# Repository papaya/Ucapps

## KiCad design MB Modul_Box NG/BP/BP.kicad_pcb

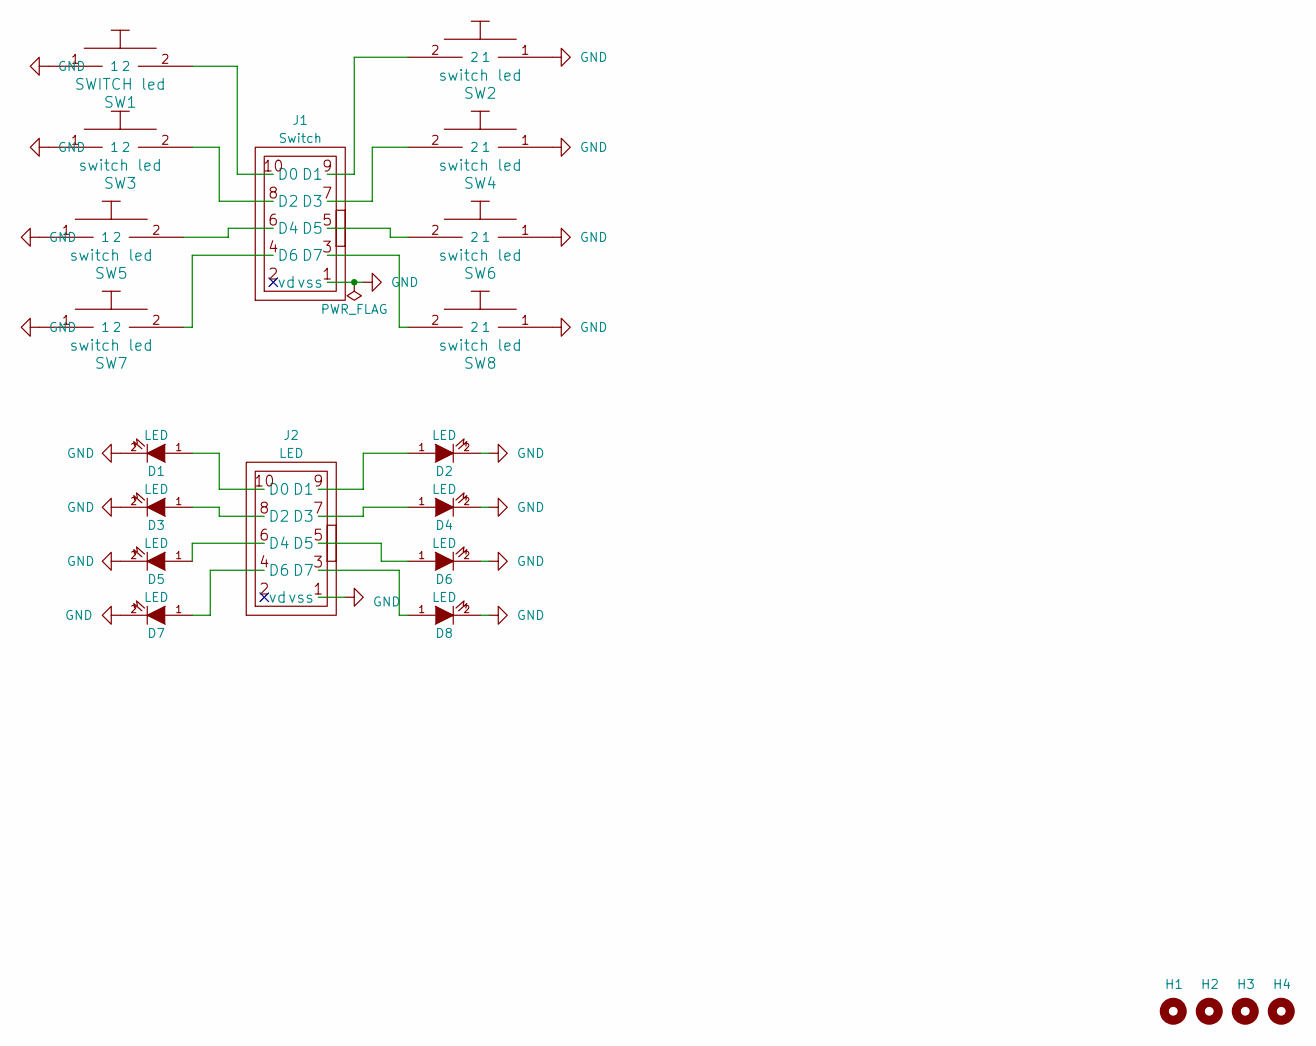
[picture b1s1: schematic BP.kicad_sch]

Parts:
D1, D2, D3, D4, D5, D6, D7, D8: LED; LED Switch mec
H1, H2, H3, H4: MountingHole; MountingHole_3.2mm_M3
J1, J2: IDC-Header_2x05_P2.54mm_Vertical
SW1: SWITCH led; switch_led_mec
SW2, SW3, SW4, SW5, SW6, SW7, SW8: switch led; switch_led_mec

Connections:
GND: D1.2 (K), D2.2 (K), D3.2 (K), D4.2 (K), D5.2 (K), D6.2 (K), D7.2 (K), D8.2 (K), J1.1 (vss), J2.1 (vss), SW1.1, SW2.1, SW3.1, SW4.1, SW5.1, SW6.1, SW7.1, SW8.1
unnamed: D1.1 (A), J2.10 (D0)
unnamed: D2.1 (A), J2.9 (D1)
unnamed: D3.1 (A), J2.8 (D2)
unnamed: D4.1 (A), J2.7 (D3)
unnamed: D5.1 (A), J2.6 (D4)
unnamed: D6.1 (A), J2.5 (D5)
unnamed: D7.1 (A), J2.4 (D6)
unnamed: D8.1 (A), J2.3 (D7)
unnamed: J1.10 (D0), SW1.2
unnamed: J1.9 (D1), SW2.2
unnamed: J1.8 (D2), SW3.2
unnamed: J1.7 (D3), SW4.2
unnamed: J1.6 (D4), SW5.2
unnamed: J1.5 (D5), SW6.2
unnamed: J1.4 (D6), SW7.2
unnamed: J1.3 (D7), SW8.2

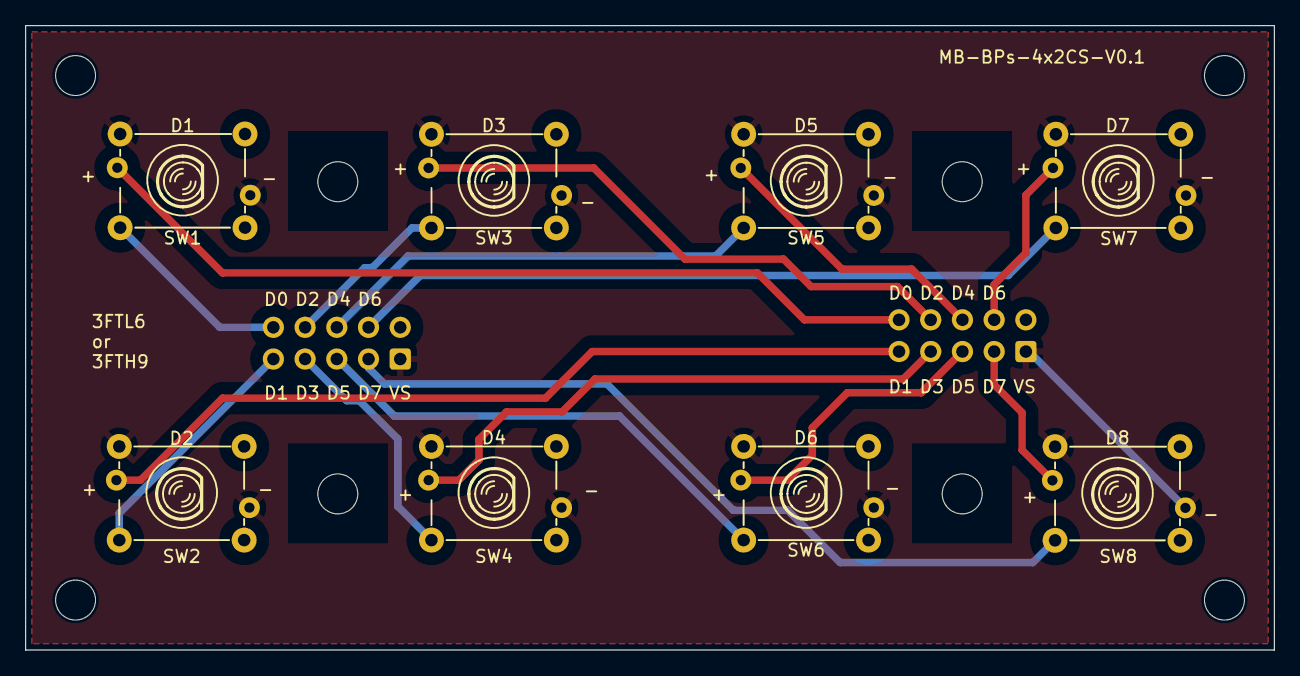
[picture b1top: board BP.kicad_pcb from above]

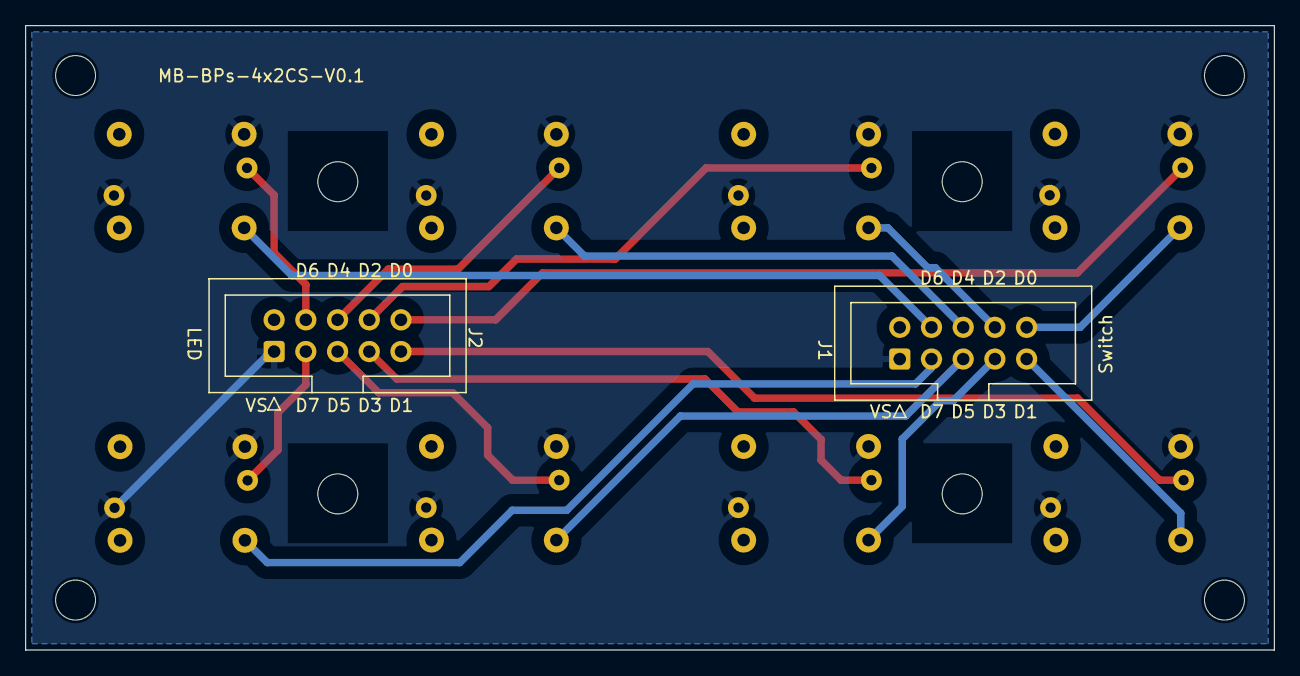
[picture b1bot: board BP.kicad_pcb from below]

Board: 2 copper layers, 100.0 x 50.0 mm, 26 parts (2 on the bottom side), 17 nets.

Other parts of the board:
H1#2, H2#2, H3#2, H4#2: MountingHole; MountingHole_3.2mm_M3

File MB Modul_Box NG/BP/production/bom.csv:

Designator,Footprint,Quantity,Value,LCSC Part #
"D1, D2, D3, D4, D5, D6, D7, D8",LED Switch mec,8,LED,
ENC1,EC12E24204A8,1,MENU,
"H1_3, H1_2, H1, H2_3, H2_2, H2, H3_3, H3_2, H3, H4_3, H4_2, H4",MountingHole_3.2mm_M3,12,MountingHole,
"J1, J2_2, J2",IDC-Header_2x05_P2.54mm_Vertical,3,IDC-Header_2x05_P2.54mm_Vertical,
"SW1, SW2, SW3, SW4, SW5, SW6, SW7, SW8",switch_led_mec,8,SWITCH led,
SWc1,124110828,1,shift,
SWc2,124110828,1,soft4,
SWc3,124110828,1,soft 3,
SWc4,124110828,1,soft 2,
SWc5,124110828,1,soft 1,
SWc6,124110828,1,MENU,

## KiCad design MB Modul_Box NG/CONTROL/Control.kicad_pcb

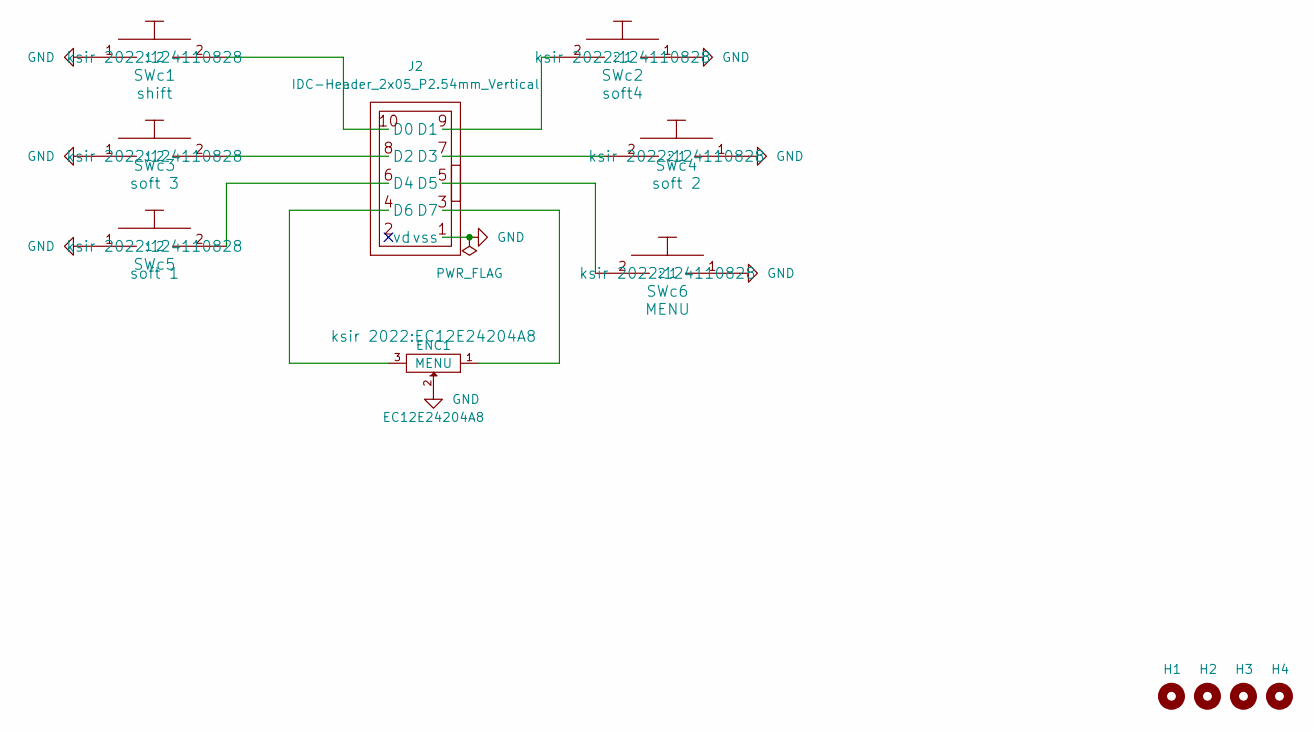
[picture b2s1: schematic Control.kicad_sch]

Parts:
ENC1: MENU; EC12E24204A8
H1, H2, H3, H4: MountingHole; MountingHole_3.2mm_M3
J2: IDC-Header_2x05_P2.54mm_Vertical
SWc1: shift; 124110828
SWc2: soft4; 124110828
SWc3: soft 3; 124110828
SWc4: soft 2; 124110828
SWc5: soft 1; 124110828
SWc6: MENU; 124110828

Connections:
GND: ENC1.2, J2.1 (vss), SWc1.1, SWc2.1, SWc3.1, SWc4.1, SWc5.1, SWc6.1
unnamed: J2.10 (D0), SWc1.2
unnamed: J2.9 (D1), SWc2.2
unnamed: J2.8 (D2), SWc3.2
unnamed: J2.7 (D3), SWc4.2
unnamed: J2.6 (D4), SWc5.2
unnamed: J2.5 (D5), SWc6.2
unnamed: ENC1.3, J2.4 (D6)
unnamed: ENC1.1, J2.3 (D7)

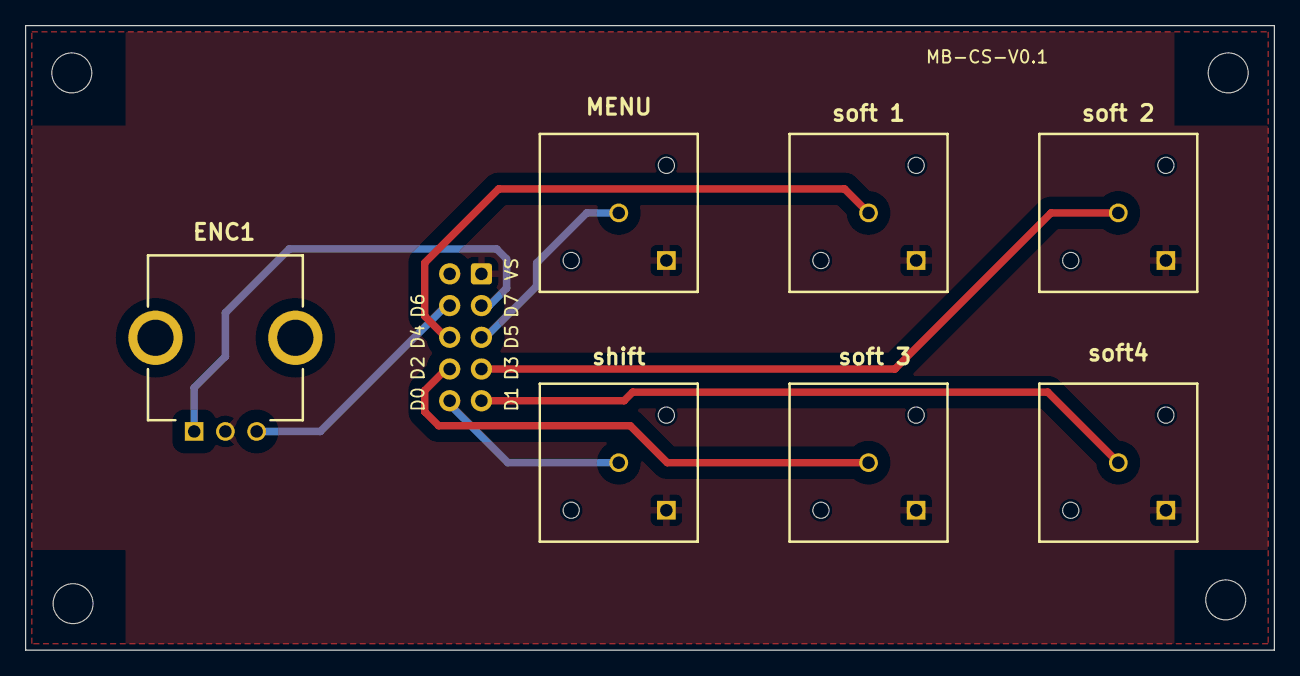
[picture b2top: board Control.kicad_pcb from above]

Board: 2 copper layers, 100.0 x 50.0 mm, 12 parts (1 on the bottom side), 9 nets.

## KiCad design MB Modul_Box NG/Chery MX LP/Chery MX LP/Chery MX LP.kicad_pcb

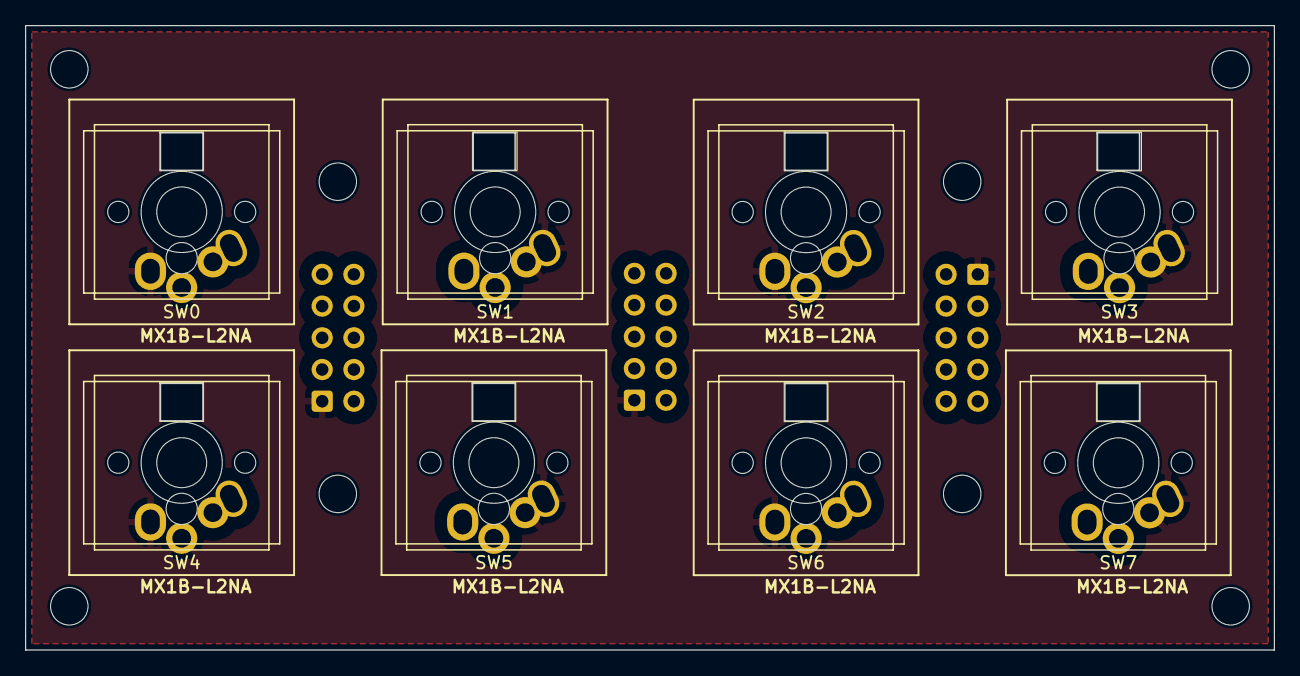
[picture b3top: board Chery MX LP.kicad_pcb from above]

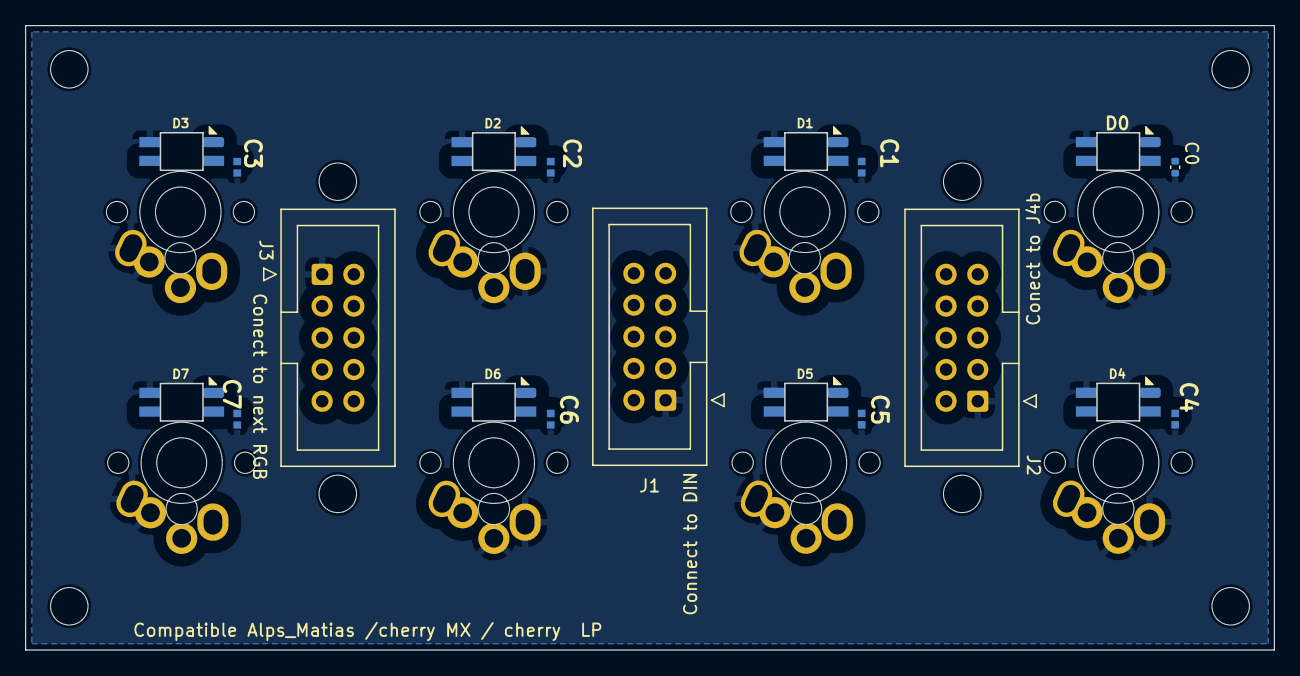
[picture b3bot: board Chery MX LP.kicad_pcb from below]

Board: 2 copper layers, 100.0 x 50.0 mm, 35 parts (19 on the bottom side), 19 nets, no tracks yet.

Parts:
C0: 100nf; C_0402_1005Metric
C1, C2, C3, C4, C5, C6, C7: 100nf; CAPC1005X55N
D0, D1, D2, D3, D4, D5, D6, D7: SK6812MINI-E; SK6812-MINI-E
H1, H2, H3, H4, H5, H6, H7, H8: MountingHole; MountingHole_3mm
J1, J2, J3: IDC-Header_2x05_P2.54mm_Vertical
SW0, SW1, SW2, SW3, SW4, SW5, SW6, SW7: CHERRY MX1B-52NA; SW_Alps_Matias_1.00u_cherry_LP

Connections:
+5V: C0.2, C1.2, C2.2, C3.2, C4.2, C5.2, C6.2, C7.2, D0.4 (VDD), D1.4 (VDD), D2.4 (VDD), D3.4 (VDD), D4.4 (VDD), D5.4 (VDD), D6.4 (VDD), D7.4 (VDD), J2.10 (VD), J3.10 (VD)
GND: C0.1, C1.1, C2.1, C3.1, C4.1, C5.1, C6.1, C7.1, D0.2 (GND), D1.2 (GND), D2.2 (GND), D3.2 (GND), D4.2 (GND), D5.2 (GND), D6.2 (GND), D7.2 (GND), J1.1 (vss), J2.1 (vss), J3.1 (vss), SW0.1 (A), SW1.2 (B), SW2.1 (A), SW3.2 (B), SW4.1 (A), SW5.2 (B), SW6.1 (A), SW7.2 (B)
unnamed: D0.3 (DI), J2.6 (SC)
unnamed: D0.1 (DO), D1.3 (DI)
unnamed: D1.1 (DO), D2.3 (DI)
unnamed: D2.1 (DO), D3.3 (DI)
unnamed: D3.1 (DO), D4.3 (DI)
unnamed: D4.1 (DO), D5.3 (DI)
unnamed: D5.1 (DO), D6.3 (DI)
unnamed: D6.1 (DO), D7.3 (DI)
unnamed: D7.1 (DO), J3.6 (SC)
unnamed: J1.10 (D0), SW0.2 (B)
unnamed: J1.9 (D1), SW1.1 (A)
unnamed: J1.8 (D2), SW2.2 (B)
unnamed: J1.7 (D3), SW3.1 (A)
unnamed: J1.6 (D4), SW4.2 (B)
unnamed: J1.5 (D5), SW5.1 (A)
unnamed: J1.4 (D6), SW6.2 (B)
unnamed: J1.3 (D7), SW7.1 (A)

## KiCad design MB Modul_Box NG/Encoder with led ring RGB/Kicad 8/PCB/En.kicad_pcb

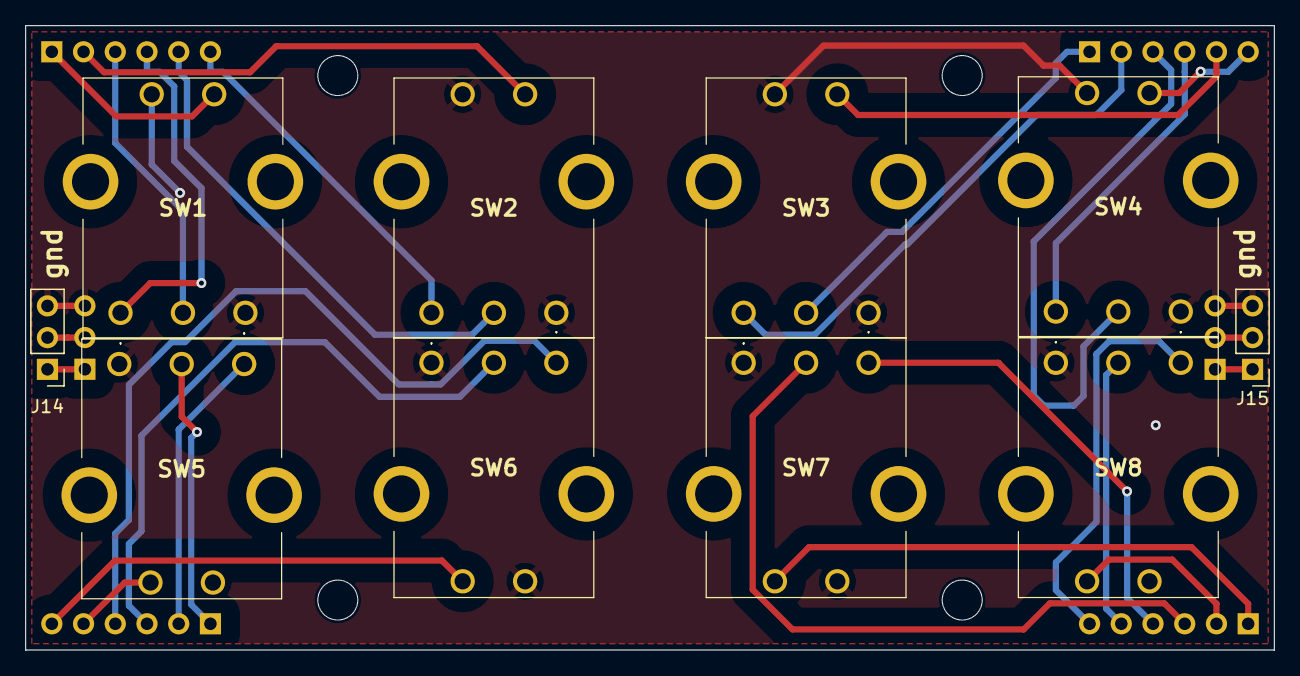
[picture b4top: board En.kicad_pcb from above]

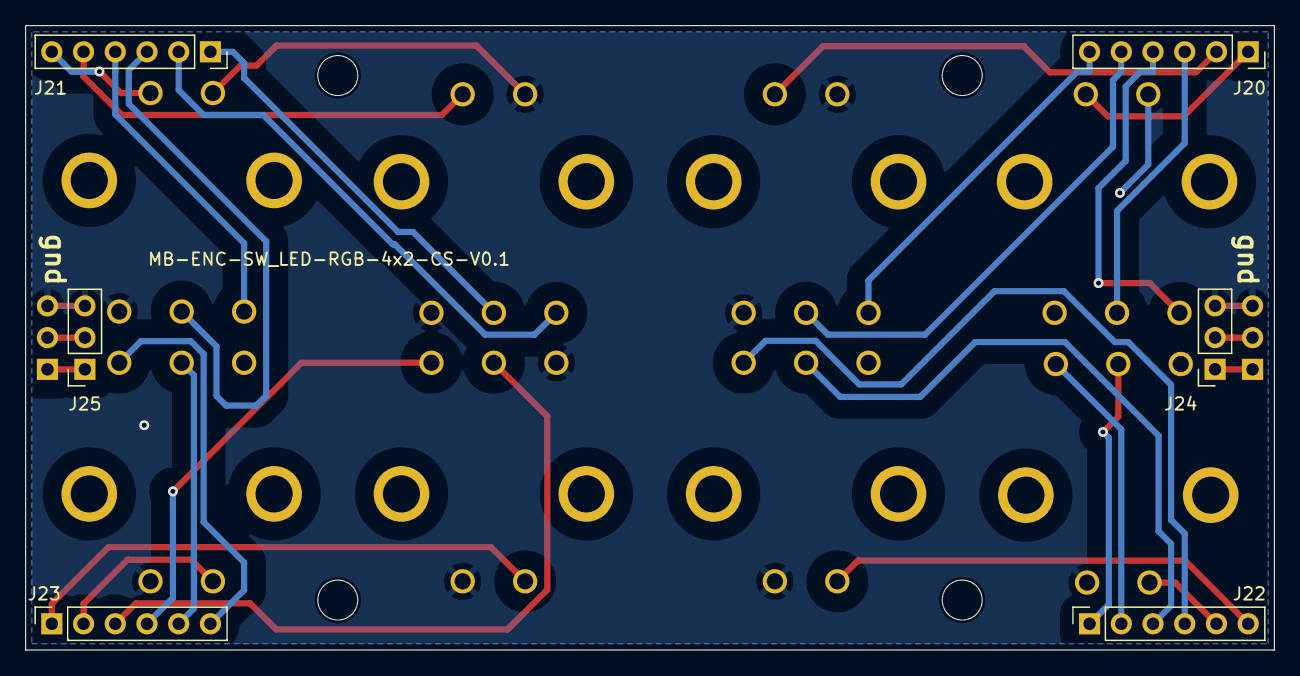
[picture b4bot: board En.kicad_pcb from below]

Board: 2 copper layers, 100.0 x 50.0 mm, 20 parts (6 on the bottom side), 29 nets.

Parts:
H13, H15, H17, H19: MountingHole; MountingHole_3.2mm_M3
J14, J15: Conn_01x06_Pin; PinHeader_1x03_P2.54mm_Vertical
J20, J21, J22, J23: Conn_01x06_Socket; PinSocket_1x06_P2.54mm_Vertical
J24, J25: Conn_01x06_Socket; PinSocket_1x03_P2.54mm_Vertical
SW1, SW2, SW3, SW4, SW5, SW6, SW7, SW8: PEC16-4XXXF-SXXXX; PEC164120FS0012

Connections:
ENC1A: J20.4, SW1.A
ENC1B: J20.3, SW1.B
ENC2A: J20.6, SW2.A
ENC2B: J20.5, SW2.B
ENC3A: J21.2, SW3.A
ENC3B: J21.1, SW3.B
ENC4A: J21.4, SW4.A
ENC4B: J21.3, SW4.B
ENC5A: J22.2, SW5.A
ENC5B: J22.1, SW5.B
ENC6A: J22.4, SW6.A
ENC6B: J22.3, SW6.B
ENC7A: J23.4, SW7.A
ENC7B: J23.3, SW7.B
ENC8A: J23.6, SW8.A
ENC8B: J23.5, SW8.B
GND1: J14.3, J15.3, J24.3, J25.3, SW1.C, SW1.S1, SW2.C, SW2.S1, SW3.C, SW3.S1, SW4.C, SW4.S1, SW5.C, SW5.S1, SW6.C, SW6.S1, SW7.C, SW7.S1, SW8.C, SW8.S1
unnamed: J14.1, J24.1
unnamed: J14.2, J24.2
unnamed: J15.1, J25.1
unnamed: J15.2, J25.2
SW1: J20.1, SW1.S2
SW2: J20.2, SW2.S2
SW3: J21.5, SW3.S2
SW4: J21.6, SW4.S2
SW5: J22.5, SW5.S2
SW6: J22.6, SW6.S2
SW7: J23.1, SW7.S2
SW8: J23.2, SW8.S2

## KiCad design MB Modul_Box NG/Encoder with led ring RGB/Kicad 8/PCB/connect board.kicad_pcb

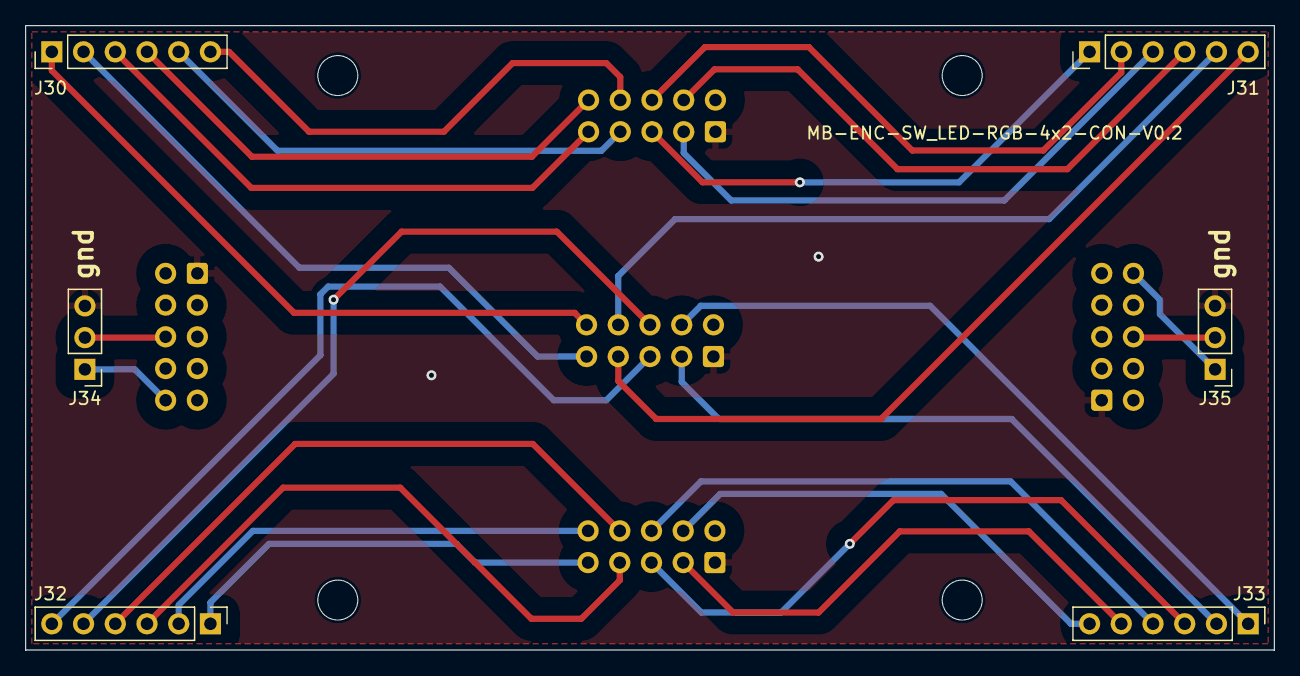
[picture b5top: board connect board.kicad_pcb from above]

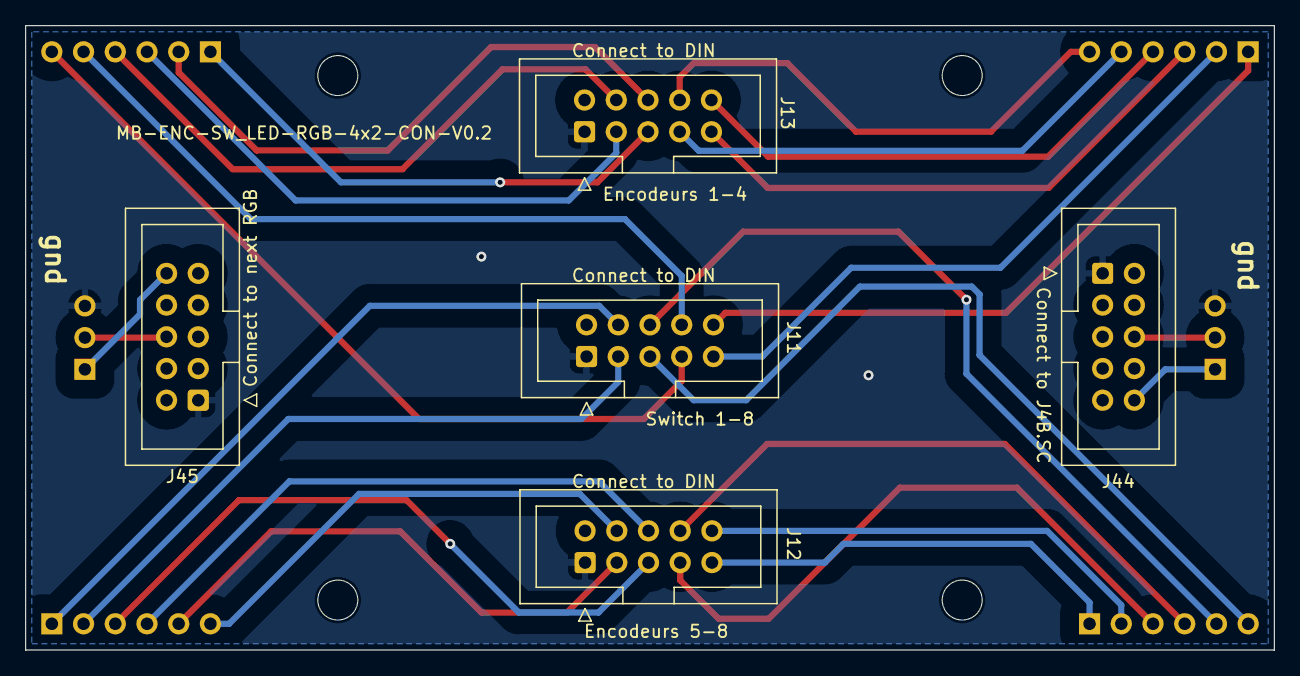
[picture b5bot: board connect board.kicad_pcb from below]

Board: 2 copper layers, 100.0 x 50.0 mm, 15 parts (5 on the bottom side), 29 nets.

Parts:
H14, H16, H18, H20: MountingHole; MountingHole_3.2mm_M3
J11, J12, J13: sin_in; IDC-Header_2x05_P2.54mm_Vertical_ksr_dIN
J30, J31, J32, J33: Conn_01x06_Pin; PinHeader_1x06_P2.54mm_Vertical
J34, J35: Conn_01x06_Pin; PinHeader_1x03_P2.54mm_Vertical
J44, J45: IDC-Header_2x05_P2.54mm_Vertical

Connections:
+5VA: J34.1, J44.10
+5VD: J35.1, J45.10
C_ENC1A: J13.10, J30.4
C_ENC1B: J13.9, J30.3
C_ENC2A: J13.8, J30.6
C_ENC2B: J13.7, J30.5
C_ENC3A: J13.6, J31.2
C_ENC3B: J13.5, J31.1
C_ENC4A: J13.4, J31.4
C_ENC4B: J13.3, J31.3
C_ENC5A: J12.10, J32.2
C_ENC5B: J12.9, J32.1
C_ENC6A: J12.8, J32.4
C_ENC6B: J12.7, J32.3
C_ENC7A: J12.6, J33.4
C_ENC7B: J12.5, J33.3
C_ENC8A: J12.4, J33.6
C_ENC8B: J12.3, J33.5
C_SW1: J11.10, J30.1
C_SW2: J11.9, J30.2
C_SW3: J11.8, J31.5
C_SW4: J11.7, J31.6
C_SW5: J11.6, J32.5
C_SW6: J11.5, J32.6
C_SW7: J11.4, J33.1
C_SW8: J11.3, J33.2
GNDA: J11.1, J12.1, J13.1, J34.3, J35.3, J44.1, J45.1
unnamed: J34.2, J44.6
unnamed: J35.2, J45.6

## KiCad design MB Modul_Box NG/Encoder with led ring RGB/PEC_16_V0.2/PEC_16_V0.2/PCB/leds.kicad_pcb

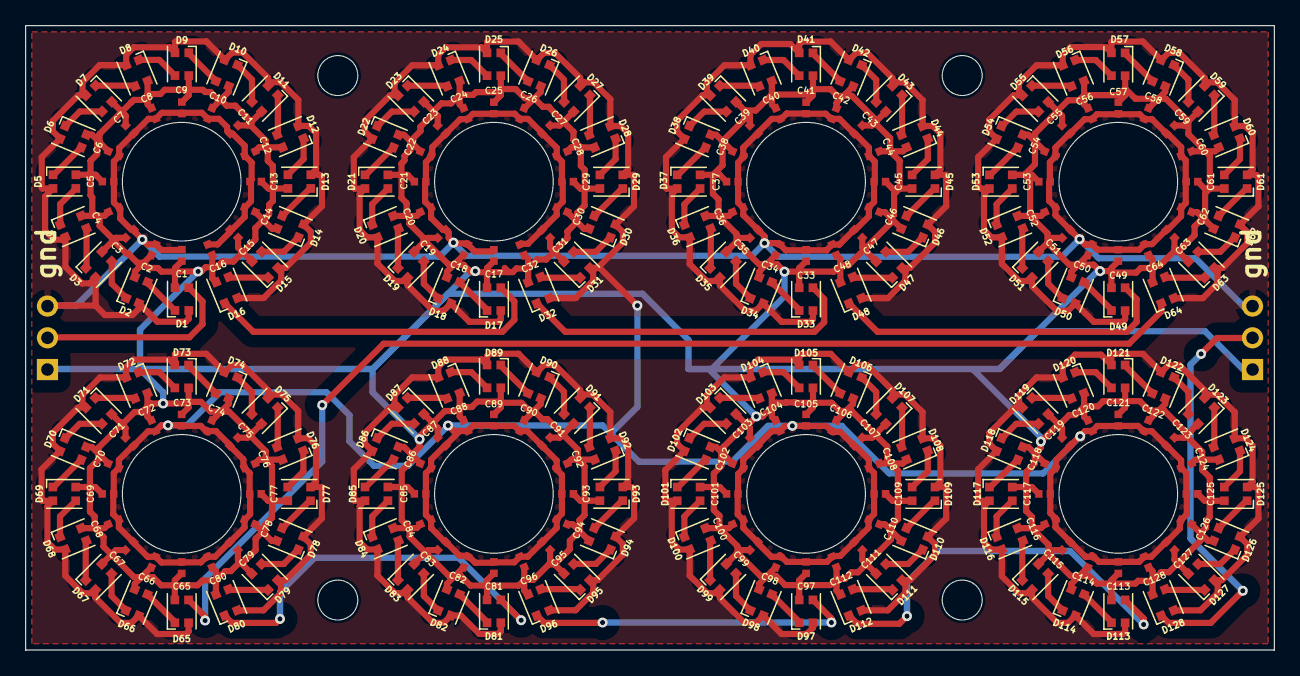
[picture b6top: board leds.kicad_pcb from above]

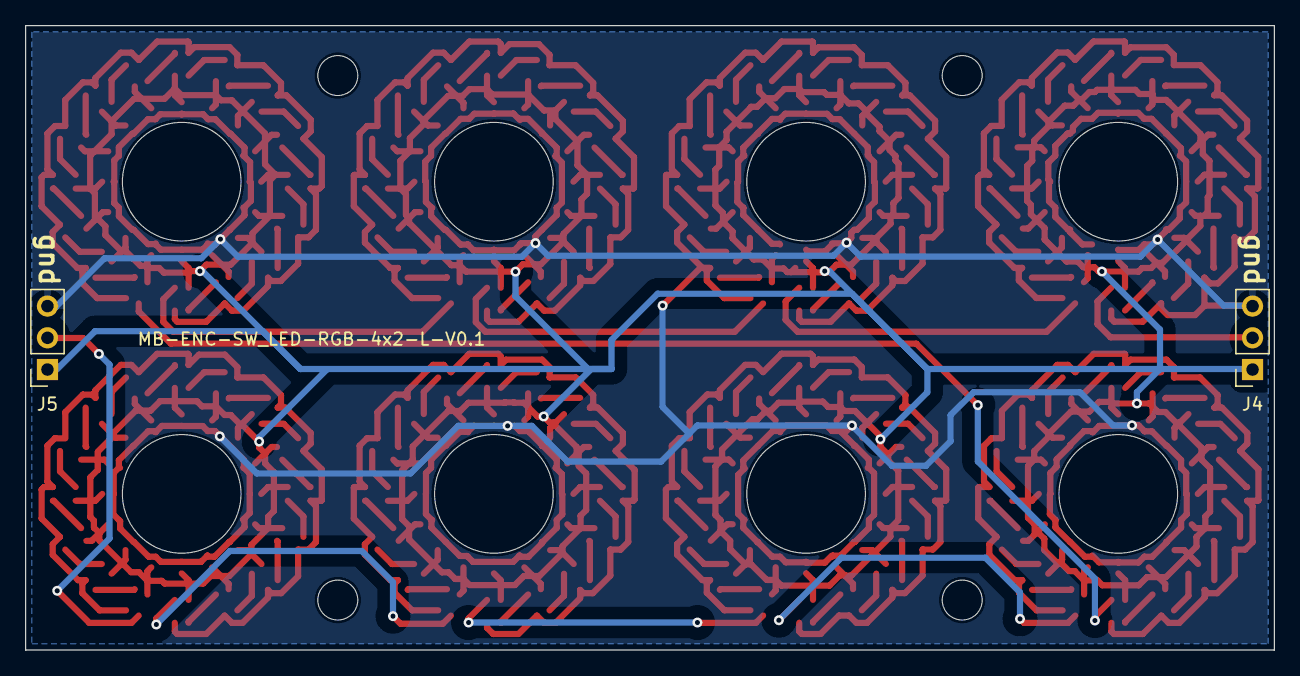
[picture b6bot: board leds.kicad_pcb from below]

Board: 2 copper layers, 100.0 x 50.0 mm, 270 parts (2 on the bottom side), 131 nets.

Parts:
C1, C2, C3, C4, C5, C6, C7, C8, C9, C10, C11, C12, C13, C14, C15, C16, C17, C18, C19, C20, C21, C22, C23, C24, C25, C26, C27, C28, C29, C30, C31, C32, C33, C34, C35, C36, C37, C38, C39, C40, C41, C42, C43, C44, C45, C46, C47, C48, C49, C50, C51, C52, C53, C54, C55, C56, C57, C58, C59, C60, C61, C62, C63, C64, C65, C66, C67, C68, C69, C70, C71, C72, C73, C74, C75, C76, C77, C78, C79, C80, C81, C82, C83, C84, C85, C86, C87, C88, C89, C90, C91, C92, C93, C94, C95, C96, C97, C98, C99, C100, C101, C102, C103, C104, C105, C106, C107, C108, C109, C110, C111, C112, C113, C114, C115, C116, C117, C118, C119, C120, C121, C122, C123, C124, C125, C126, C127, C128: 100nf; CAPC1005X55N
D1, D2, D3, D4, D5, D6, D7, D8, D9, D10, D11, D12, D13, D14, D15, D16, D17, D18, D19, D20, D21, D22, D23, D24, D25, D26, D27, D28, D29, D30, D31, D32, D33, D34, D35, D36, D37, D38, D39, D40, D41, D42, D43, D44, D45, D46, D47, D48, D49, D50, D51, D52, D53, D54, D55, D56, D57, D58, D59, D60, D61, D62, D63, D64, D65, D66, D67, D68, D69, D70, D71, D72, D73, D74, D75, D76, D77, D78, D79, D80, D81, D82, D83, D84, D85, D86, D87, D88, D89, D90, D91, D92, D93, D94, D95, D96, D97, D98, D99, D100, D101, D102, D103, D104, D105, D106, D107, D108, D109, D110, D111, D112, D113, D114, D115, D116, D117, D118, D119, D120, D121, D122, D123, D124, D125, D126, D127, D128: WS2812-2020; LED_WS2812B-2020_PLCC4_2.0x2.0mm
H1, H2, H3, H4: MountingHole; MountingHole_3.2mm_M3
H5, H6, H7, H8, H9, H10, H11, H12: MountingHole; Hole_9.5mm
J4, J5: Conn_01x06_Socket; PinSocket_1x03_P2.54mm_Vertical

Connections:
+5V: C1.2, C2.2, C3.2, C4.2, C5.2, C6.2, C7.2, C8.2, C9.2, C10.2, C11.2, C12.2, C13.2, C14.2, C15.2, C16.2, C17.2, C18.2, C19.2, C20.2, C21.2, C22.2, C23.2, C24.2, C25.2, C26.2, C27.2, C28.2, C29.2, C30.2, C31.2, C32.2, C33.2, C34.2, C35.2, C36.2, C37.2, C38.2, C39.2, C40.2, C41.2, C42.2, C43.2, C44.2, C45.2, C46.2, C47.2, C48.2, C49.2, C50.2, C51.2, C52.2, C53.2, C54.2, C55.2, C56.2, C57.2, C58.2, C59.2, C60.2, C61.2, C62.2, C63.2, C64.2, C65.2, C66.2, C67.2, C68.2, C69.2, C70.2, C71.2, C72.2, C73.2, C74.2, C75.2, C76.2, C77.2, C78.2, C79.2, C80.2, C81.2, C82.2, C83.2, C84.2, C85.2, C86.2, C87.2, C88.2, C89.2, C90.2, C91.2, C92.2, C93.2, C94.2, C95.2, C96.2, C97.2, C98.2, C99.2, C100.2, C101.2, C102.2, C103.2, C104.2, C105.2, C106.2, C107.2, C108.2, C109.2, C110.2, C111.2, C112.2, C113.2, C114.2, C115.2, C116.2, C117.2, C118.2, C119.2, C120.2, C121.2, C122.2, C123.2, C124.2, C125.2, C126.2, C127.2, C128.2, D1.4 (VDD), D2.4 (VDD), D3.4 (VDD), D4.4 (VDD), D5.4 (VDD), D6.4 (VDD), D7.4 (VDD), D8.4 (VDD), D9.4 (VDD), D10.4 (VDD), D11.4 (VDD), D12.4 (VDD), D13.4 (VDD), D14.4 (VDD), D15.4 (VDD), D16.4 (VDD), D17.4 (VDD), D18.4 (VDD), D19.4 (VDD), D20.4 (VDD), D21.4 (VDD), D22.4 (VDD), D23.4 (VDD), D24.4 (VDD), D25.4 (VDD), D26.4 (VDD), D27.4 (VDD), D28.4 (VDD), D29.4 (VDD), D30.4 (VDD), D31.4 (VDD), D32.4 (VDD), D33.4 (VDD), D34.4 (VDD), D35.4 (VDD), D36.4 (VDD), D37.4 (VDD), D38.4 (VDD), D39.4 (VDD), D40.4 (VDD), D41.4 (VDD), D42.4 (VDD), D43.4 (VDD), D44.4 (VDD), D45.4 (VDD), D46.4 (VDD), D47.4 (VDD), D48.4 (VDD), D49.4 (VDD), D50.4 (VDD), D51.4 (VDD), D52.4 (VDD), D53.4 (VDD), D54.4 (VDD), D55.4 (VDD), D56.4 (VDD), D57.4 (VDD), D58.4 (VDD), D59.4 (VDD), D60.4 (VDD), D61.4 (VDD), D62.4 (VDD), D63.4 (VDD), D64.4 (VDD), D65.4 (VDD), D66.4 (VDD), D67.4 (VDD), D68.4 (VDD), D69.4 (VDD), D70.4 (VDD), D71.4 (VDD), D72.4 (VDD), D73.4 (VDD), D74.4 (VDD), D75.4 (VDD), D76.4 (VDD), D77.4 (VDD), D78.4 (VDD), D79.4 (VDD), D80.4 (VDD), D81.4 (VDD), D82.4 (VDD), D83.4 (VDD), D84.4 (VDD), D85.4 (VDD), D86.4 (VDD), D87.4 (VDD), D88.4 (VDD), D89.4 (VDD), D90.4 (VDD), D91.4 (VDD), D92.4 (VDD), D93.4 (VDD), D94.4 (VDD), D95.4 (VDD), D96.4 (VDD), D97.4 (VDD), D98.4 (VDD), D99.4 (VDD), D100.4 (VDD), D101.4 (VDD), D102.4 (VDD), D103.4 (VDD), D104.4 (VDD), D105.4 (VDD), D106.4 (VDD), D107.4 (VDD), D108.4 (VDD), D109.4 (VDD), D110.4 (VDD), D111.4 (VDD), D112.4 (VDD), D113.4 (VDD), D114.4 (VDD), D115.4 (VDD), D116.4 (VDD), D117.4 (VDD), D118.4 (VDD), D119.4 (VDD), D120.4 (VDD), D121.4 (VDD), D122.4 (VDD), D123.4 (VDD), D124.4 (VDD), D125.4 (VDD), D126.4 (VDD), D127.4 (VDD), D128.4 (VDD), J4.1, J5.1
GND: C1.1, C2.1, C3.1, C4.1, C5.1, C6.1, C7.1, C8.1, C9.1, C10.1, C11.1, C12.1, C13.1, C14.1, C15.1, C16.1, C17.1, C18.1, C19.1, C20.1, C21.1, C22.1, C23.1, C24.1, C25.1, C26.1, C27.1, C28.1, C29.1, C30.1, C31.1, C32.1, C33.1, C34.1, C35.1, C36.1, C37.1, C38.1, C39.1, C40.1, C41.1, C42.1, C43.1, C44.1, C45.1, C46.1, C47.1, C48.1, C49.1, C50.1, C51.1, C52.1, C53.1, C54.1, C55.1, C56.1, C57.1, C58.1, C59.1, C60.1, C61.1, C62.1, C63.1, C64.1, C65.1, C66.1, C67.1, C68.1, C69.1, C70.1, C71.1, C72.1, C73.1, C74.1, C75.1, C76.1, C77.1, C78.1, C79.1, C80.1, C81.1, C82.1, C83.1, C84.1, C85.1, C86.1, C87.1, C88.1, C89.1, C90.1, C91.1, C92.1, C93.1, C94.1, C95.1, C96.1, C97.1, C98.1, C99.1, C100.1, C101.1, C102.1, C103.1, C104.1, C105.1, C106.1, C107.1, C108.1, C109.1, C110.1, C111.1, C112.1, C113.1, C114.1, C115.1, C116.1, C117.1, C118.1, C119.1, C120.1, C121.1, C122.1, C123.1, C124.1, C125.1, C126.1, C127.1, C128.1, D1.2 (GND), D2.2 (GND), D3.2 (GND), D4.2 (GND), D5.2 (GND), D6.2 (GND), D7.2 (GND), D8.2 (GND), D9.2 (GND), D10.2 (GND), D11.2 (GND), D12.2 (GND), D13.2 (GND), D14.2 (GND), D15.2 (GND), D16.2 (GND), D17.2 (GND), D18.2 (GND), D19.2 (GND), D20.2 (GND), D21.2 (GND), D22.2 (GND), D23.2 (GND), D24.2 (GND), D25.2 (GND), D26.2 (GND), D27.2 (GND), D28.2 (GND), D29.2 (GND), D30.2 (GND), D31.2 (GND), D32.2 (GND), D33.2 (GND), D34.2 (GND), D35.2 (GND), D36.2 (GND), D37.2 (GND), D38.2 (GND), D39.2 (GND), D40.2 (GND), D41.2 (GND), D42.2 (GND), D43.2 (GND), D44.2 (GND), D45.2 (GND), D46.2 (GND), D47.2 (GND), D48.2 (GND), D49.2 (GND), D50.2 (GND), D51.2 (GND), D52.2 (GND), D53.2 (GND), D54.2 (GND), D55.2 (GND), D56.2 (GND), D57.2 (GND), D58.2 (GND), D59.2 (GND), D60.2 (GND), D61.2 (GND), D62.2 (GND), D63.2 (GND), D64.2 (GND), D65.2 (GND), D66.2 (GND), D67.2 (GND), D68.2 (GND), D69.2 (GND), D70.2 (GND), D71.2 (GND), D72.2 (GND), D73.2 (GND), D74.2 (GND), D75.2 (GND), D76.2 (GND), D77.2 (GND), D78.2 (GND), D79.2 (GND), D80.2 (GND), D81.2 (GND), D82.2 (GND), D83.2 (GND), D84.2 (GND), D85.2 (GND), D86.2 (GND), D87.2 (GND), D88.2 (GND), D89.2 (GND), D90.2 (GND), D91.2 (GND), D92.2 (GND), D93.2 (GND), D94.2 (GND), D95.2 (GND), D96.2 (GND), D97.2 (GND), D98.2 (GND), D99.2 (GND), D100.2 (GND), D101.2 (GND), D102.2 (GND), D103.2 (GND), D104.2 (GND), D105.2 (GND), D106.2 (GND), D107.2 (GND), D108.2 (GND), D109.2 (GND), D110.2 (GND), D111.2 (GND), D112.2 (GND), D113.2 (GND), D114.2 (GND), D115.2 (GND), D116.2 (GND), D117.2 (GND), D118.2 (GND), D119.2 (GND), D120.2 (GND), D121.2 (GND), D122.2 (GND), D123.2 (GND), D124.2 (GND), D125.2 (GND), D126.2 (GND), D127.2 (GND), D128.2 (GND), J4.3, J5.3
unnamed: D1.3 (DI), J4.2
unnamed: D1.1 (DO), D2.3 (DI)
unnamed: D2.1 (DO), D3.3 (DI)
unnamed: D3.1 (DO), D4.3 (DI)
unnamed: D4.1 (DO), D5.3 (DI)
unnamed: D5.1 (DO), D6.3 (DI)
unnamed: D6.1 (DO), D7.3 (DI)
unnamed: D7.1 (DO), D8.3 (DI)
unnamed: D8.1 (DO), D9.3 (DI)
unnamed: D9.1 (DO), D10.3 (DI)
unnamed: D10.1 (DO), D11.3 (DI)
unnamed: D11.1 (DO), D12.3 (DI)
unnamed: D12.1 (DO), D13.3 (DI)
unnamed: D13.1 (DO), D14.3 (DI)
unnamed: D14.1 (DO), D15.3 (DI)
unnamed: D15.1 (DO), D16.3 (DI)
unnamed: D16.1 (DO), D17.3 (DI)
unnamed: D17.1 (DO), D18.3 (DI)
unnamed: D18.1 (DO), D19.3 (DI)
unnamed: D19.1 (DO), D20.3 (DI)
unnamed: D20.1 (DO), D21.3 (DI)
unnamed: D21.1 (DO), D22.3 (DI)
unnamed: D22.1 (DO), D23.3 (DI)
unnamed: D23.1 (DO), D24.3 (DI)
unnamed: D24.1 (DO), D25.3 (DI)
unnamed: D25.1 (DO), D26.3 (DI)
unnamed: D26.1 (DO), D27.3 (DI)
unnamed: D27.1 (DO), D28.3 (DI)
unnamed: D28.1 (DO), D29.3 (DI)
unnamed: D29.1 (DO), D30.3 (DI)
unnamed: D30.1 (DO), D31.3 (DI)
unnamed: D31.1 (DO), D32.3 (DI)
unnamed: D32.1 (DO), D33.3 (DI)
unnamed: D33.1 (DO), D34.3 (DI)
unnamed: D34.1 (DO), D35.3 (DI)
unnamed: D35.1 (DO), D36.3 (DI)
unnamed: D36.1 (DO), D37.3 (DI)
unnamed: D37.1 (DO), D38.3 (DI)
unnamed: D38.1 (DO), D39.3 (DI)
unnamed: D39.1 (DO), D40.3 (DI)
unnamed: D40.1 (DO), D41.3 (DI)
unnamed: D41.1 (DO), D42.3 (DI)
unnamed: D42.1 (DO), D43.3 (DI)
unnamed: D43.1 (DO), D44.3 (DI)
unnamed: D44.1 (DO), D45.3 (DI)
unnamed: D45.1 (DO), D46.3 (DI)
unnamed: D46.1 (DO), D47.3 (DI)
unnamed: D47.1 (DO), D48.3 (DI)
unnamed: D48.1 (DO), D49.3 (DI)
unnamed: D49.1 (DO), D50.3 (DI)
unnamed: D50.1 (DO), D51.3 (DI)
unnamed: D51.1 (DO), D52.3 (DI)
unnamed: D52.1 (DO), D53.3 (DI)
unnamed: D53.1 (DO), D54.3 (DI)
unnamed: D54.1 (DO), D55.3 (DI)
unnamed: D55.1 (DO), D56.3 (DI)
unnamed: D56.1 (DO), D57.3 (DI)
unnamed: D57.1 (DO), D58.3 (DI)
unnamed: D58.1 (DO), D59.3 (DI)
unnamed: D59.1 (DO), D60.3 (DI)
unnamed: D60.1 (DO), D61.3 (DI)
unnamed: D61.1 (DO), D62.3 (DI)
unnamed: D62.1 (DO), D63.3 (DI)
unnamed: D63.1 (DO), D64.3 (DI)
unnamed: D64.1 (DO), D65.3 (DI)
unnamed: D65.1 (DO), D66.3 (DI)
unnamed: D66.1 (DO), D67.3 (DI)
unnamed: D67.1 (DO), D68.3 (DI)
unnamed: D68.1 (DO), D69.3 (DI)
unnamed: D69.1 (DO), D70.3 (DI)
unnamed: D70.1 (DO), D71.3 (DI)
unnamed: D71.1 (DO), D72.3 (DI)
unnamed: D72.1 (DO), D73.3 (DI)
unnamed: D73.1 (DO), D74.3 (DI)
unnamed: D74.1 (DO), D75.3 (DI)
unnamed: D75.1 (DO), D76.3 (DI)
unnamed: D76.1 (DO), D77.3 (DI)
unnamed: D77.1 (DO), D78.3 (DI)
unnamed: D78.1 (DO), D79.3 (DI)
unnamed: D79.1 (DO), D80.3 (DI)
unnamed: D80.1 (DO), D81.3 (DI)
unnamed: D81.1 (DO), D82.3 (DI)
unnamed: D82.1 (DO), D83.3 (DI)
unnamed: D83.1 (DO), D84.3 (DI)
unnamed: D84.1 (DO), D85.3 (DI)
unnamed: D85.1 (DO), D86.3 (DI)
unnamed: D86.1 (DO), D87.3 (DI)
unnamed: D87.1 (DO), D88.3 (DI)
unnamed: D88.1 (DO), D89.3 (DI)
unnamed: D89.1 (DO), D90.3 (DI)
unnamed: D90.1 (DO), D91.3 (DI)
unnamed: D91.1 (DO), D92.3 (DI)
unnamed: D92.1 (DO), D93.3 (DI)
unnamed: D93.1 (DO), D94.3 (DI)
unnamed: D94.1 (DO), D95.3 (DI)
unnamed: D95.1 (DO), D96.3 (DI)
unnamed: D96.1 (DO), D97.3 (DI)
unnamed: D97.1 (DO), D98.3 (DI)
unnamed: D98.1 (DO), D99.3 (DI)
unnamed: D99.1 (DO), D100.3 (DI)
unnamed: D100.1 (DO), D101.3 (DI)
unnamed: D101.1 (DO), D102.3 (DI)
unnamed: D102.1 (DO), D103.3 (DI)
unnamed: D103.1 (DO), D104.3 (DI)
unnamed: D104.1 (DO), D105.3 (DI)
unnamed: D105.1 (DO), D106.3 (DI)
unnamed: D106.1 (DO), D107.3 (DI)
unnamed: D107.1 (DO), D108.3 (DI)
unnamed: D108.1 (DO), D109.3 (DI)
unnamed: D109.1 (DO), D110.3 (DI)
unnamed: D110.1 (DO), D111.3 (DI)
unnamed: D111.1 (DO), D112.3 (DI)
unnamed: D112.1 (DO), D113.3 (DI)
unnamed: D113.1 (DO), D114.3 (DI)
unnamed: D114.1 (DO), D115.3 (DI)
unnamed: D115.1 (DO), D116.3 (DI)
unnamed: D116.1 (DO), D117.3 (DI)
unnamed: D117.1 (DO), D118.3 (DI)
unnamed: D118.1 (DO), D119.3 (DI)
unnamed: D119.1 (DO), D120.3 (DI)
unnamed: D120.1 (DO), D121.3 (DI)
unnamed: D121.1 (DO), D122.3 (DI)
unnamed: D122.1 (DO), D123.3 (DI)
unnamed: D123.1 (DO), D124.3 (DI)
unnamed: D124.1 (DO), D125.3 (DI)
unnamed: D125.1 (DO), D126.3 (DI)
unnamed: D126.1 (DO), D127.3 (DI)
unnamed: D127.1 (DO), D128.3 (DI)
unnamed: D128.1 (DO), J5.2

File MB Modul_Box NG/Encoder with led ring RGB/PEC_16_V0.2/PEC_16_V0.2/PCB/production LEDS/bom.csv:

Designator,Footprint,Quantity,Value,LCSC Part #
"C1, C10, C100, C101, C102, C103, C104, C105, C106, C107, C108, C109, C11, C110, C111, C112, C113, C114, C115, C116, C117, C118, C119, C12, C120, C121, C122, C123, C124, C125, C126, C127, C128, C13, C14, C15, C16, C17, C18, C19, C2, C20, C21, C22, C23, C24, C25, C26, C27, C28, C29, C3, C30, C31, C32, C33, C34, C35, C36, C37, C38, C39, C4, C40, C41, C42, C43, C44, C45, C46, C47, C48, C49, C5, C50, C51, C52, C53, C54, C55, C56, C57, C58, C59, C6, C60, C61, C62, C63, C64, C65, C66, C67, C68, C69, C7, C70, C71, C72, C73, C74, C75, C76, C77, C78, C79, C8, C80, C81, C82, C83, C84, C85, C86, C87, C88, C89, C9, C90, C91, C92, C93, C94, C95, C96, C97, C98, C99",CAPC1005X55N,128,100nf,C1525
"D1, D10, D100, D101, D102, D103, D104, D105, D106, D107, D108, D109, D11, D110, D111, D112, D113, D114, D115, D116, D117, D118, D119, D12, D120, D121, D122, D123, D124, D125, D126, D127, D128, D13, D14, D15, D16, D17, D18, D19, D2, D20, D21, D22, D23, D24, D25, D26, D27, D28, D29, D3, D30, D31, D32, D33, D34, D35, D36, D37, D38, D39, D4, D40, D41, D42, D43, D44, D45, D46, D47, D48, D49, D5, D50, D51, D52, D53, D54, D55, D56, D57, D58, D59, D6, D60, D61, D62, D63, D64, D65, D66, D67, D68, D69, D7, D70, D71, D72, D73, D74, D75, D76, D77, D78, D79, D8, D80, D81, D82, D83, D84, D85, D86, D87, D88, D89, D9, D90, D91, D92, D93, D94, D95, D96, D97, D98, D99",LED_WS2812B-2020_PLCC4_2.0x2.0mm,128,WS2812-2020,C2976072
"H1, H2, H3, H4",MountingHole_3.2mm_M3,4,MountingHole,
"H10, H11, H12, H5, H6, H7, H8, H9",Hole_9.5mm,8,MountingHole,
"J4, J5",PinSocket_1x03_P2.54mm_Vertical,2,Conn_01x06_Socket,
